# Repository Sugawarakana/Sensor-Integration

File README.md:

## Note: This project has been migrated into ULDSG

# Integrated Sensor Board for Battery Off-Gas Monitoring

A compact PCB and firmware stack that integrates multiple gas sensors and a battery off-gas detector onto one board, developed as part of a collaborative research project between the **University of Michigan**, **Universitat Politecnica Valencia**, and **UL Research Institutes**. The board targets applications in **battery safety**, **robotics**, and **energy storage system** environments where real-time multi-gas monitoring in constrained spaces is critical.

## Project Overview

The board consolidates multiple commerically-available gas sensors that detect hydrogen (H₂), carbon monoxide (CO), carbon dioxide (CO₂), volatile organic compounds (VOC), methane (CH₄), and electrolyte-vapor onto a single PCB, interfacing through **two independent CAN buses**, **I²C**, and an **analog ADC** channel. The controller is an **STM32 Nucleo-G431KB**, chosen for its native FDCAN peripheral, I²C support, and 12-bit ADC.

Since the Nucleo-G431KB has only one CAN controller, the two buses run at different bit rates on different hardware:

- **FDCAN1 @ 500 kbps** — Telaire T3650 and SGX-BLD2, through an on-board CAN transceiver.
- **MCP2515 @ 250 kbps** (SPI) — Li-ion Tamer, which requires its own 250 kbps segment.

The project spans: **PCB design** (Autodesk Eagle), **embedded firmware** ([OffgasMonitor.ino](OffgasMonitor/OffgasMonitor.ino), with non-blocking dual-CAN, dual-sensor I²C and ADC acquisition, byte-level protocol decoding, and on-chip health monitoring), and a **Python data-acquisition pipeline** ([serial_logger.py](OffgasMonitor/serial_logger.py), with serial parsing into a wide-table CSV).

## Specifications

| Parameter | Detail |
|---|---|
| **Controller** | STM32 Nucleo-G431KB (ARM Cortex-M4) |
| **Layers** | 1-layer PCB |
| **Board Thickness** | 1.6 mm (JLCPCB default) |
| **Power Supply** | 12 V battery input via terminal blocks |
| **Communication** | FDCAN1 (500 kbps), MCP2515 CAN (250 kbps) over SPI, I²C (100 kHz), analog ADC |
| **Log Rate** | 1 Hz (`LOG_INTERVAL = 1000 ms`) |
| **Serial** | 115200 baud |
| **Fabrication** | JLCPCB |

## Sensor Summary

| Sensor | Measurement | Interface | Address / ID | Power |
|---|---|---|---|---|
| Telaire T3650 | H₂, pressure, humidity, temperature | FDCAN1 @ 500 kbps | `0x18FF0CEB` (J1939, ext.) | 12 V direct |
| SGX-BLD2 | H₂ %, CO level, status flags | FDCAN1 @ 500 kbps | `0x256` (standard) | 12 V direct |
| Li-ion Tamer | Electrolyte-vapor off-gas, state, temperature | CAN @ 250 kbps via MCP2515 (SPI) | PGN `0xFF01` (J1939, ext.) | 12 V direct |
| MiCS-VZ-89TE | CO₂-equivalent & VOC | I²C | — | 3.3 V (Nucleo output) |
| MP7227 | CH₄ (methane) | Analog → ADC (`A0`) | — | 3.0 V (MIC5233 LDO) |
| SEN66 | PM1.0/2.5/4.0/10, RH, T, VOC & NOx index, NDIR CO₂ | I²C @ 100 kHz | `0x6B` | 3.3 V (buck from 12 V) |

> **Note:** the MiCS-VZ-89TE CO₂ figure is a CO₂-*equivalent* derived from its VOC channel, not a real CO₂ measurement. The SEN66 carries the true NDIR CO₂ reading; both are logged side by side (`co2_ppm` vs `sen66_co2_ppm`).

## Power Architecture

```
12V Supply
  │
  ├──[Terminal Blocks]──► Telaire T3650 (H₂)      — 12V direct
  ├──[Terminal Blocks]──► SGX-BLD2 (CO/H₂)        — 12V direct
  ├──[CAN Terminal]─────► Li-ion Tamer (off-gas)  — 12V direct
  │
  ├──► Buck regulator ──► 3.3V ──► SEN66 (PM/RH/T/VOC/NOx/CO₂)
  │
  └──► Buck regulator ──► 5V ──► Nucleo-G431KB (onboard regulator)
                                  └──► 3.3V ──► MiCS-VZ-89TE (CO₂ & VOC)
                                  └──► 3.3V ──► MIC5233 LDO ──► 3.0V ──► MP7227 (CH₄)
```

The SEN66 runs from its own buck rail rather than the Nucleo's 3.3 V output: its fan and
heater draw far more than the on-board regulator can supply. Only its I²C lines and ground
are shared with the MCU.

## Signal Chain

- **Telaire T3650 & SGX-BLD2:** CAN → on-board transceiver → **FDCAN1 @ 500 kbps** → MCU.
- **Li-ion Tamer:** CAN @ **250 kbps** → **MCP2515** controller → **SPI1** → MCU.
- **MiCS-VZ-89TE:** **I²C** directly to the MCU.
- **SEN66:** **I²C** to the MCU, sharing the bus with the MiCS-VZ-89TE. The bus is clamped to **100 kHz** (`Wire.setClock(100000)`) — that is the SEN66's ceiling, and the MiCS is comfortable at that rate.
- **MP7227 (CH₄):** analog output → zeroed via potentiometer → amplified (ADA4528 precision op-amp stage with HF filtering) → **ADC** (`A0`, 12-bit). Sensor rail from the **MIC5233** LDO.

### Li-ion Tamer → Power / CAN bus

| Li-ion Tamer pin | Connects to | Target terminal | Notes |
|---|---|---|---|
| Vin | PCB | 12 V (CAN terminal) | Supply positive |
| GND | PCB | GND (CAN terminal) | Supply / common ground |
| CANH | MCP2515 module | CANH | CAN differential high |
| CANL | MCP2515 module | CANL | CAN differential low |

### MCP2515 → Nucleo (SPI)

| MCP2515 pin | Nucleo pin | Type | Notes |
|---|---|---|---|
| SCK (18) | `PB3` / D13 | SPI clock | SPI1 default |
| MOSI (19) | `PB5` / D11 | Master out, slave in | SPI1 default |
| MISO (16) | `PB4` / D12 | Master in, slave out | SPI1 default |
| CS (20) | `PA8` / **D9** | Chip select | D9 instead of the default D10, which is `fdcan1_rx` |
| INT (21) | `PB0` / **D3** | Interrupt input | D3 instead of the default D2, which is `fdcan1_tx` |
| VCC / GND | 3V3 / GND | Power | Shared ground with the CAN terminal ground |
| RST | NRST | Reset | Pull-up reset |
| — | CAN ground | Power | GND (CAN terminal) |

The MCP2515 module runs from a **16 MHz** crystal (`QUARTZ_FREQUENCY`); the firmware prints whether the requested 250 kbps is an exact bit rate at boot.

## Design Highlights

- **Sensor placement:** all gas inlets sit along the board edges to maximize exposure and airflow.
- **Unidirectional signal flow:** voltage and signal routing follows a single direction across the board for a clean layout and easy debugging.
- **Ground stability:** a large copper pour provides a solid ground plane and minimizes ground bounce.
- **Filtering:** decoupling capacitors and filtering suppress high-frequency noise on power and signal lines.
- **Differential pair integrity:** CANH/CANL pairs are routed with controlled impedance and matched length.
- **Mechanical:** mounting holes for integration into enclosures or test fixtures.

## Firmware — `OffgasMonitor/OffgasMonitor.ino`

A single non-blocking acquisition loop that services two CAN buses, two I²C sensors, and the ADC, then emits one human-readable report per second.

### Architecture

- **Continuous CAN polling.** `pollAllCan()` drains both receive FIFOs completely on every loop iteration, so neither bus backs up while the report is being printed. It is called again immediately after `logData()` to catch frames that arrived during printing.
- **Non-blocking SEN66 startup.** `setup()` only issues the `deviceReset()`; the 1.2 s settling time, the `startContinuousMeasurement()` call, and the 1.1 s first-frame delay are stepped through by a `SEN66_RESET → SEN66_WAIT → SEN66_RUN` state machine inside `pollSen66()`, so no `delay()` ever stalls the CAN buses. A failed start is simply retried on the next 1.2 s tick.
- **Drift-free I²C sampling.** In `SEN66_RUN` the read deadline advances by a fixed `SEN66_PERIOD_MS` rather than reloading from `millis()`, so the sampling instant does not creep with the ~100 ms `logData()` spends on serial output; it resyncs only if it falls more than a full period behind. One read is ~2–3 ms of bus traffic at 100 kHz — short enough for the 32-slot FDCAN FIFO and the interrupt-driven MCP2515 buffer to absorb whatever arrives meanwhile.
- **Latest-frame slots.** Each CAN device gets a `Latest<T>` slot holding the most recent frame of the current cycle plus a `valid` flag. The flag is cleared after every report, so **a device that stays silent for a second leaves its section out of the output entirely** — silence is preserved as a diagnostic rather than being masked by stale data.
- **Age-based staleness for the SEN66.** The SEN66 deliberately does *not* use a `Latest<>` slot. It produces exactly one frame per second — the same rate as the log cycle — so a clear-every-cycle flag would make its block blink in and out as the two 1 Hz clocks drift past each other. Instead the last sample is kept with its `millis()` timestamp and reported with a `STALE` status once it ages past `SEN66_STALE_MS` (2.5 s), which points at I²C or power rather than at normal jitter.
- **CAN polling during ADC averaging.** `readAvgPolled()` averages 16 ADC samples to suppress noise; the ~200 µs settling gap between samples is spent polling CAN instead of idling. Averaging 16 samples across 2 channels takes ≈ 6.4 ms, which is too long to leave the buses unattended.
- **Rollover-safe scheduling.** The 1 Hz cadence uses a signed `millis()` comparison against `g_nextLog`, so it survives the 49-day `millis()` rollover, and the deadline advances by a fixed `LOG_INTERVAL` rather than from "now" to avoid drift.
- **Boot markers.** Setup prints tagged progress lines `A: boot` → `G: setup done` (`A` serial, `B` FDCAN1, `C` MCP2515, `D` I²C/ADC, `E` SEN66 reset + serial number, `F` die-temp calibration constants, `G` done), giving both a human and the Python logger an unambiguous reboot marker.

### Decoding

- **SGX-BLD2 (`0x256`)** — temperature (offset −55 °C), H₂ % (16-bit, ×0.01), an 8-bit status byte decoded bit-by-bit into named faults, supply voltage, humidity, roll counter, and CO level.
- **Telaire T3650 (`0x18FF0CEB`)** — pressure (16-bit LE, ×0.0078125 − 250 kPa), humidity (×0.4 %), H₂ concentration (×0.0025 %), temperature (×0.03125 − 273 °C), and a raw status byte.
- **Li-ion Tamer (PGN `0xFF01`)** — J1939 source address from the low ID byte, state (`Illegal / Error / Warmup / Normal / Alarm`), signed temperature, and a signed 16-bit off-gas scalar (÷100). The report is annotated `<<< ALARM` in the Alarm state, or flagged when the scalar reaches the alarm trigger level of 1.0.
- **SEN66 (I²C `0x6B`)** — PM1.0 / PM2.5 / PM4.0 / PM10 (µg/m³), relative humidity, temperature, VOC index, NOx index, and NDIR CO₂, read through the Sensirion float API.
- **Unknown frames** on either bus are captured and printed with bus name, ID, and raw data bytes, so an unexpected node on the wire is visible instead of silently dropped.

### SEN66 "unknown value" handling

The Sensirion float API divides each raw 16-bit word by its scale factor, so an unavailable channel surfaces as a plausible-looking number rather than `NaN`: `0xFFFF / 10 = 6553.5` for PM, `0x7FFF / 100 = 327.67` for RH/T, `0x7FFF / 10 = 3276.7` for the gas indices, and `0xFFFF` for CO₂. `printSen66Value()` compares against those sentinels and prints **`n/a`**, so a dead channel can never be mistaken for a real 6553.5 µg/m³ or 3276.7 index reading. Two status lines qualify the block further:

| Line | Meaning |
|---|---|
| `SEN66: no valid frame yet (starting up / running)` | Printed instead of the whole block; no frame has ever been read |
| `SEN66 Status:  gas index warming up` | VOC or NOx index still reads a hard 0 — VOC settles toward 100 over tens of seconds, NOx toward 1 after ~10–15 s |
| `SEN66 Status:  STALE, frame age <n> ms` | The cached frame is older than 2.5 s — check I²C wiring and the 3.3 V buck rail |

### Board health monitoring

Each cycle also reports the MCU's own condition using the internal channels and STM32G4 factory calibration constants:

1. **Actual VDDA** is back-computed from the internal reference (`VREFINT_CAL` at 3.0 V) — the reference voltage is fixed, so a lower reading implies a higher supply.
2. **Junction temperature (Tj)** is derived by normalizing the temperature-sensor reading to the 3.0 V calibration reference and interpolating between the factory `TS_CAL1` (30 °C) and `TS_CAL2` (130 °C) points.
3. Running **max Tj** and **min VDDA** are tracked across the whole run, and the status line reports `OK` / `HIGH` (> 60 °C) / `OVERHEAT` (> 85 °C).

Tj is die temperature, not ambient, and factory calibration is only accurate to roughly ±5 °C — it is a "is the board cooking?" check, not an ambient-temperature log.

### Serial output format

One block per second, sections separated by `=============================`. Each round begins with `Raw ADC Value:`, which the Python logger uses as the round boundary:

```
Raw ADC Value: 2048
Voltage: 1.650 V
=============================
Board health (STM32G431KB):
Die Temp:           42.3 C
Die Temp Max:       44.1 C
VDDA:               3298 mV
VDDA Min:           3290 mV
ADC raw (ts/vref):  1035/1512
Board Status:       OK
=============================
CO2 equ(ppm): 412 ppm
VOC(isobutylene) equ: 87 ppb
=============================
Message received from SEN66:
PM1.0:              0.0 ug/m3
PM2.5:              0.0 ug/m3
PM4.0:              0.0 ug/m3
PM10:               0.0 ug/m3
Humidity:           54.5 %
Temperature:        25.38 C
VOC Index:          0.0
NOx Index:          0.0
CO2:                431 ppm
SEN66 Status:       gas index warming up
=============================
Message received from SGX-BLD2:
...
=============================
Message received from Telaire T3650:
...
=============================
Message received from Li-ion Tamer:
Tamer SA=0xEB  State=Normal  Temp=24C  OffGas=0.12
=============================
```

## Host Data Acquisition — `OffgasMonitor/serial_logger.py`

A dependency-light (`pyserial` only) logger that parses the live serial stream and aggregates each one-second round into a single wide-table CSV row.

```bash
pip install pyserial

python serial_logger.py                 # use the PORT default in the file (COM3)
python serial_logger.py COM3            # specify the port
python serial_logger.py /dev/ttyACM0
python serial_logger.py --list-ports    # list available ports
python serial_logger.py --auto          # auto-pick a port that looks like an STM32
python serial_logger.py --selftest      # no hardware needed; verify parsing on built-in samples
```

| Flag | Effect |
|---|---|
| `--baud` | Baud rate (default 115200) |
| `--prefix` | Output filename prefix (default `sensor_log`; the start time is appended) |
| `--auto` | Pick the STMicroelectronics VID/description port automatically |
| `--list-ports` | List ports and exit |
| `--no-raw` | Skip the timestamped raw-text `.log` alongside the CSV |
| `--no-reconnect` | Exit on a dropout instead of retrying every 2 s |
| `--quiet` | Do not echo each row to the console |
| `--selftest` | Run the parser over built-in samples and check every field |

### Behavior

- **Section state machine.** The firmware reuses labels across sections (`Voltage:` appears under both ADC and SGX; `Temperature:` / `Humidity:` under SGX, Telaire *and* SEN66), so the parser disambiguates by *which section it is currently in*; a separator line clears the section and prevents bleed-over. Two label collisions are handled explicitly: `VOC(` anchors the MiCS reading so the SEN66's `VOC Index:` cannot overwrite it, and the colon in `SEN66:` distinguishes the no-frame one-liner from the in-block `SEN66 Status:` line.
- **Numbers are read after the last colon.** `num()` only searches the tail of a line, so digits inside a label — the 2 in `CO2`/`H2`, the 1.0 in `PM1.0` — are never mistaken for the reading. A channel printed `n/a` contains no digits and therefore lands as an empty cell.
- **Empty means silent.** ADC, board health, and I²C columns are populated every round. If one of the CAN devices sent nothing that second, its columns are left **empty on purpose** — that emptiness is the record that the device was offline, so it must not be forward-filled in post-processing. The `can_device` column lists which devices were heard from that round.
- **Empty SEN66 columns mean something else.** Because the SEN66 is on I²C, its block is present every round once running, so blank value columns are a fault rather than a silent bus. `sen66_status` says which: `NO_FRAME` (not started yet), `WARMUP` (gas-index algorithm not converged), or `STALE` with `sen66_age_ms` giving the age of the cached frame. Statuses accumulate semicolon-separated, since the firmware can print more than one in a round.
- **Fault flags reassembled.** Individual SGX flag lines are collected into a semicolon-separated `sgx_flags` list *and* re-packed into `sgx_flags_hex` for easy comparison.
- **Crash-safe.** Every row is flushed to disk immediately, a Ctrl+C or serial dropout still writes the in-progress round, the port is reconnected automatically after a dropout, and board reboots (`A: boot`) are counted and reported at exit.
- **Self-test.** `--selftest` runs the parser against embedded sample output covering the normal case, an overheat + fault-flag + Tamer-alarm case, a stale SEN66 frame with an `n/a` CO₂ channel, unknown frames on both buses, and a truncated final round holding only the SEN66 no-frame one-liner — then writes `selftest_output.csv`. It needs no hardware and not even `pyserial`.

### CSV columns

| Group | Columns |
|---|---|
| Timestamp | `date`, `time` |
| ADC (A0 / CH₄) | `raw_adc`, `voltage_adc` |
| Board health | `die_temp_c`, `die_temp_max_c`, `vdda_mv`, `vdda_min_mv`, `adc_raw_ts`, `adc_raw_vref`, `board_status` |
| MiCS-VZ-89TE | `co2_ppm`, `voc_ppb` |
| SEN66 | `sen66_pm1`, `sen66_pm25`, `sen66_pm4`, `sen66_pm10`, `sen66_rh_pct`, `sen66_temp_c`, `sen66_voc_index`, `sen66_nox_index`, `sen66_co2_ppm`, `sen66_status`, `sen66_age_ms` |
| Devices heard | `can_device` |
| SGX-BLD2 | `sgx_temp_c`, `sgx_h2_pct`, `sgx_voltage_v`, `sgx_humidity_pct`, `sgx_roll_counter`, `sgx_level_co`, `sgx_flags`, `sgx_flags_hex` |
| Telaire T3650 | `tel_pressure_kpa`, `tel_humidity_pct`, `tel_h2_conc_pct`, `tel_temp_c`, `tel_status` |
| Li-ion Tamer | `tamer_sa`, `tamer_state`, `tamer_temp_c`, `tamer_offgas`, `tamer_alarm` |
| Unknown frames | `unk_fdcan_id`, `unk_fdcan_data`, `unk_mcp_id`, `unk_mcp_data` |

## Library Dependencies

| Library | Version | Purpose | Source |
|---|---|---|---|
| `ACANFD_STM32` — Pierre Molinaro | 1.1.2-rc1 | FDCAN1 @ 500 kbps (T3650, SGX-BLD2) | https://github.com/pierremolinaro/acanfd-stm32 |
| `ACAN2515` — Pierre Molinaro | 2.1.5 | MCP2515 CAN @ 250 kbps (Li-ion Tamer) | https://github.com/pierremolinaro/acan2515 |
| `MICS-VZ-89TE` — Herve Grabas | — | CO₂-equivalent & VOC over I²C | https://github.com/HGrabas/MICS-VZ-89TE |
| `arduino-i2c-sen66` — Sensirion (LeonieFierz) | — | SEN66 PM / RH / T / VOC / NOx / CO₂ over I²C | https://github.com/Sensirion/arduino-i2c-sen66 |

Board support: **STM32duino** (STM32 MCU based boards), target *Nucleo-32 / Nucleo G431KB*.

> **Build note:** the Sensirion driver and the STM32 core both define `NO_ERROR` with different values, so the sketch `#undef`s it and pins it to the Sensirion meaning (`0`) before any error check. If your `arduino-i2c-sen66` version declares `getSerialNumber(char *, uint16_t)`, drop the `(int8_t *)` cast in `setupSen66()`.

## Testing

The board was validated on an Agilent E3641A bench power supply at **12.00 V / 0.200 A**. Sensor data from all channels was streamed over USB serial and captured by the Python logger, confirming correct FDCAN, MCP2515 CAN, I²C, and ADC acquisition — real-time temperature, humidity, raw ADC values, off-gas state, and computed gas concentrations (ppm/ppb) from each module. The SEN66 draws its own 3.3 V buck rail, so the supply current rises accordingly once its fan spins up; budget for that when sizing the bench supply.

The logger's `--selftest` mode covers the whole parsing path without hardware — including the SEN66 warm-up, stale-frame, and `n/a`-channel cases — and exits non-zero on any field mismatch, so it doubles as a regression check after editing either the firmware's print strings or the parser.

## Repository Structure

| Path | Contents |
|---|---|
| [OffgasMonitor/OffgasMonitor.ino](OffgasMonitor/OffgasMonitor.ino) | Current firmware: dual CAN + I²C (MiCS-VZ-89TE, SEN66) + ADC + board health |
| [OffgasMonitor/serial_logger.py](OffgasMonitor/serial_logger.py) | Current host logger: serial → wide-table CSV |
| [schematic.pdf](schematic.pdf) / [pcb_layout.pdf](pcb_layout.pdf) | Full schematic and PCB layout (top view) |
| [guides/](guides/) | Sensor and component datasheets (T3650, SGX-BLD2, MiCS-VZ-89TE, MP7227, MIC5233, Li-ion Tamer, Nucleo-G431KB) |
| [Deprecated/PCB Design/](Deprecated/PCB%20Design/) | Autodesk Eagle sources (`.sch` / `.brd`) and JLCPCB Gerber/CAM output, by revision (3.11, 3.22, 5.1) |
| [Deprecated/modules/](Deprecated/modules/) | Superseded per-sensor firmware & logging sketches (CAN, CH₄/ADC, CO₂/I²C) |
| [Deprecated/sensor_read/](Deprecated/sensor_read/) | Superseded integrated firmware + pandas/Excel logger |

Everything under [Deprecated/](Deprecated/) is kept for reference only; the active firmware and logger live in [OffgasMonitor/](OffgasMonitor/).

## Tools & Skills

- **EDA:** Autodesk Eagle
- **Fabrication:** JLCPCB
- **Controller Platform:** STM32 Nucleo-G431KB (ARM Cortex-M4)
- **Firmware:** Arduino / STM32duino — `ACANFD_STM32` (FDCAN), `ACAN2515` (SPI CAN), `arduino-i2c-sen66` and `MICS-VZ-89TE` on a shared I²C bus, 12-bit ADC, on-chip Tj/VDDA calibration
- **Software:** Python (`pyserial`) for serial data acquisition & CSV logging
- **Skills demonstrated:** PCB design · multi-protocol embedded firmware (dual CAN / I²C / ADC) · J1939 & proprietary CAN frame decoding · non-blocking real-time acquisition · sensor data logging & diagnostics

## License

This project was developed under the University of Michigan and UL Research Institutes collaboration. Contact the author for usage permissions.

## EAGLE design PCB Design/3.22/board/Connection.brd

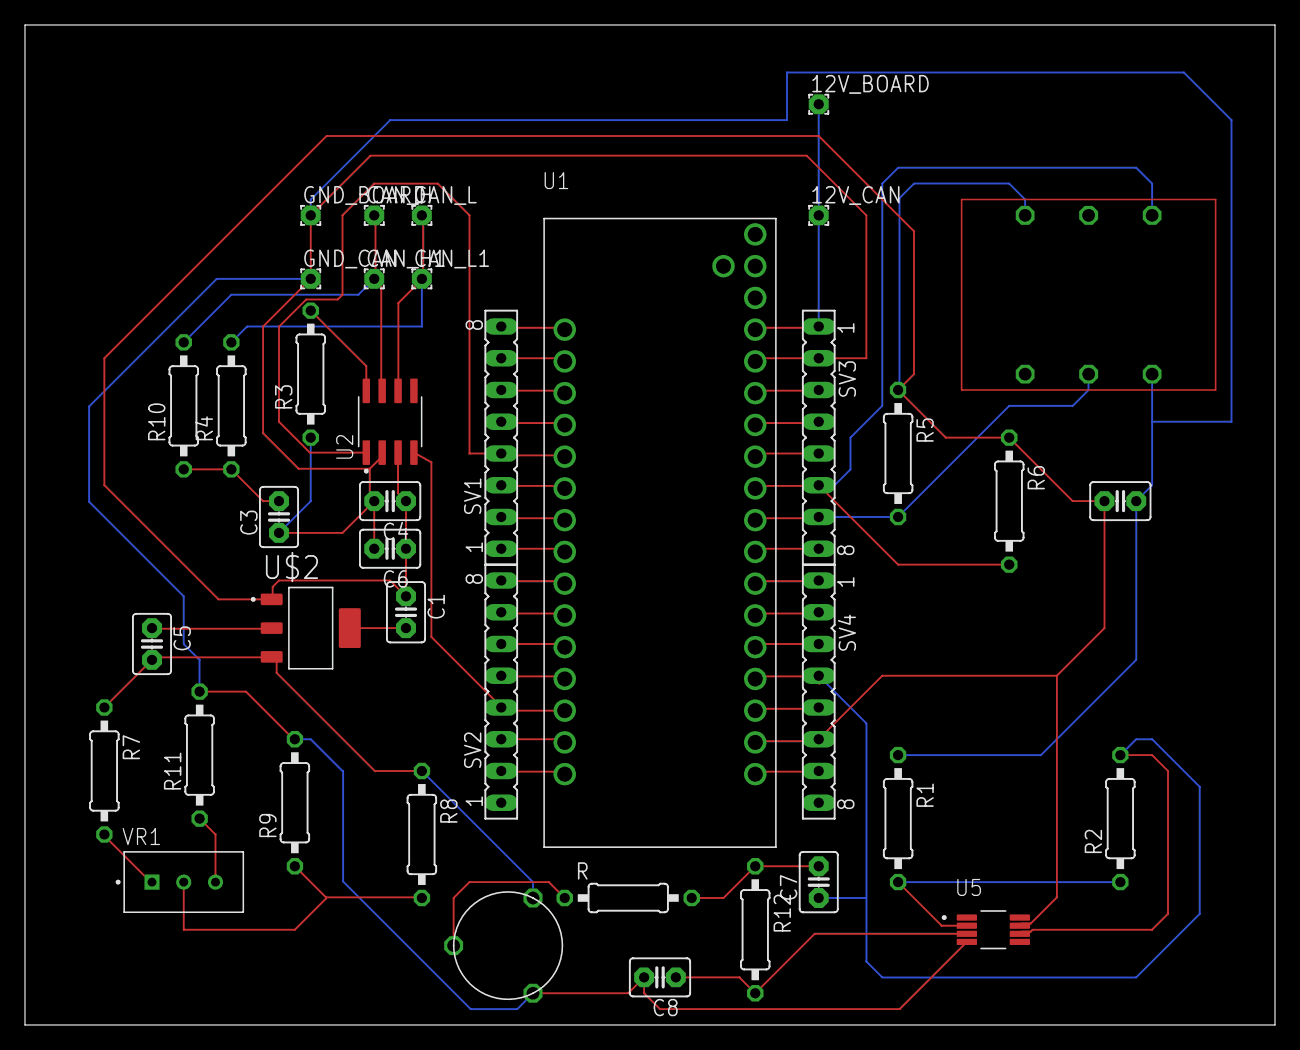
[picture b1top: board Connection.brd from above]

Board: 2 copper layers, 100.0 x 80.0 mm, 40 parts (0 on the bottom side), 44 nets.

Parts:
12V_BOARD, 12V_CAN: 1,6/0,8
C1: 1.0μF; C2.5-3
C2, C3: 0.1μF; C2.5-3
C4: 100-nF ceramic; C2.5-3
C5: 2.2μF; C2.5-3
C6: 4.7 uF; C2.5-3
C7: 680nF; C2.5-3
C8: 4.7μF; C2.5-3
CAN_H, CAN_H1: 1,6/0,8
CAN_L, CAN_L1: 1,6/0,8
GND_BOARD: 1,6/0,8
GND_CAN: 1,6/0,8
R: 6.5kΩ; 0207/10
R1, R8, R9: 1000Ω; 0207/10
R2, R12: 49000Ω; 0207/10
R3, R7, R11: 10000Ω; 0207/10
R4, R10: 60Ω; 0207/10
R5, R6: 4700; 0207/10
SV1, SV2, SV3, SV4: FE08
U1: NUCLEO-G431KB; MODULE_NUCLEO-G431KB
U2: SN65HVD230; SOIC127P599X175-8N
U5: ADA4528-1ARMZ-R7; SOP65P490X110-8N
U$1: MP7227; MP7227_FP
U$2: MIC5233-3PIN; SOT230P700X180-4N
U$4: MICS-VZ-89TE; MICS-VZ-89TE_FP
VR1: 3296W-1-203LF; TRIM_3296W-1-203LF

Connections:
GND: C2.2, C3.1, C4.2, C6.2, C8.2, GND_BOARD.1, GND_CAN.1, R1.1, R3.1, R9.2, R11.2, SV3.2, U1.CN3_2, U2.2, U5.4, U$1.P$3, U$4.P$6
unnamed: 12V_BOARD.1, 12V_CAN.1, SV3.1, U1.CN3_1
unnamed: R5.2, SV3.7, U1.CN3_7, U$4.P$5
unnamed: R6.2, SV3.6, U1.CN3_6, U$4.P$3
unnamed: R1.2, R2.1, U5.2
unnamed: R.1, U$1.P$1
unnamed: CAN_H.1, CAN_H1.1, R10.2, U2.7
unnamed: CAN_L.1, CAN_L1.1, R4.2, U2.6
unnamed: C1.1, C2.1, C4.1, C6.1, R5.1, R6.1, SV4.6, U1.CN3_14, U2.3, U5.7, U$2.1, U$4.P$1
unnamed: SV1.4, U1.CN4_5, U2.1
unnamed: SV2.4, U1.CN4_13, U2.4
unnamed: R3.2, U2.8
unnamed: C3.2, R4.1, R10.1
unnamed: C7.1, R2.2, SV4.4, U1.CN3_12, U5.6
unnamed: C5.1, U$2.2
unnamed: R8.2, R9.1, VR1.2
unnamed: C7.2, R.2, R12.1
unnamed: C5.2, R7.1, R8.1, U$1.P$2, U$2.3
unnamed: SV3.3, U1.CN3_3
unnamed: SV3.4, U1.CN3_4
unnamed: SV3.5, U1.CN3_5
unnamed: SV3.8, U1.CN3_8
unnamed: SV4.1, U1.CN3_9
unnamed: SV4.2, U1.CN3_10
unnamed: SV4.3, U1.CN3_11
unnamed: SV4.5, U1.CN3_13
unnamed: SV4.7, U1.CN3_15
unnamed: SV1.1, U1.CN4_8
unnamed: SV1.2, U1.CN4_7
unnamed: SV1.3, U1.CN4_6
unnamed: SV1.5, U1.CN4_4
unnamed: SV1.6, U1.CN4_3
unnamed: SV1.7, U1.CN4_2
unnamed: SV1.8, U1.CN4_1
unnamed: SV2.2, U1.CN4_15
unnamed: SV2.3, U1.CN4_14
unnamed: SV2.5, U1.CN4_12
unnamed: SV2.6, U1.CN4_11
unnamed: SV2.7, U1.CN4_10
unnamed: SV2.8, U1.CN4_9
unnamed: C1.2, U$2.4
unnamed: R7.2, VR1.1
unnamed: R11.1, VR1.3
unnamed: C8.1, R12.2, U5.3

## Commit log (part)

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2025-09-08 Update files
2025-11-25 Upload CAN guides
2025-11-25 11.25 Update
2025-11-25 Upload mics single
2026-02-24 Add sensor data logging functionality
    This script reads data from various sensors via a serial connection and logs the data to an Excel file. It handles data from internal sensors, SGX-BLD2, and Telaire T3650, saving entries periodically.
2026-03-13 Update of guides & PCB design
2026-03-24 Update design
2026-06-03 Upload PCB design pdf
2026-06-24 Updated designs
2026-06-24 Uploaded non-blocking design of nucleo clock
